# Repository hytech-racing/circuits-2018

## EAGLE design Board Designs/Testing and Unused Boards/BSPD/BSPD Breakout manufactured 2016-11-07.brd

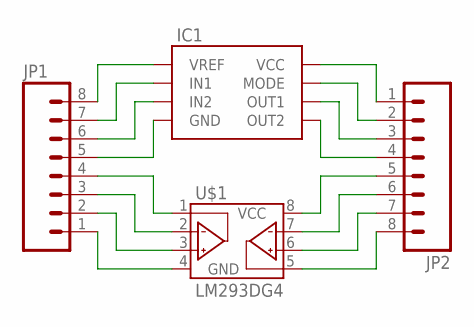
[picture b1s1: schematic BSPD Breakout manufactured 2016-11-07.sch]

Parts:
IC1: MC34161DG; SOIC-08
JP1, JP2: M08; 1X08
U$1: LM293DG4; SOIC-08

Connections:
unnamed: IC1.1 (VREF), JP1.8
unnamed: IC1.2 (IN1), JP1.7
unnamed: IC1.3 (IN2), JP1.6
unnamed: IC1.4 (GND), JP1.5
unnamed: IC1.5 (OUT2), JP2.4
unnamed: IC1.6 (OUT1), JP2.3
unnamed: IC1.7 (MODE), JP2.2
unnamed: IC1.8 (VCC), JP2.1
unnamed: JP2.5, U$1.8 (VCC)
unnamed: JP2.6, U$1.7 (2OUT)
unnamed: JP2.7, U$1.6 (2IN-)
unnamed: JP2.8, U$1.5 (2IN+)
unnamed: JP1.1, U$1.4 (GND)
unnamed: JP1.2, U$1.3 (1IN+)
unnamed: JP1.3, U$1.2 (1IN-)
unnamed: JP1.4, U$1.1 (1OUT)

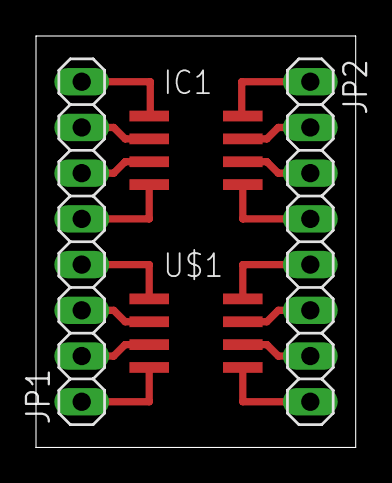
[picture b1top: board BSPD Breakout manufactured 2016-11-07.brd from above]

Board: 2 copper layers, 17.8 x 22.9 mm, 4 parts (0 on the bottom side), 16 nets.

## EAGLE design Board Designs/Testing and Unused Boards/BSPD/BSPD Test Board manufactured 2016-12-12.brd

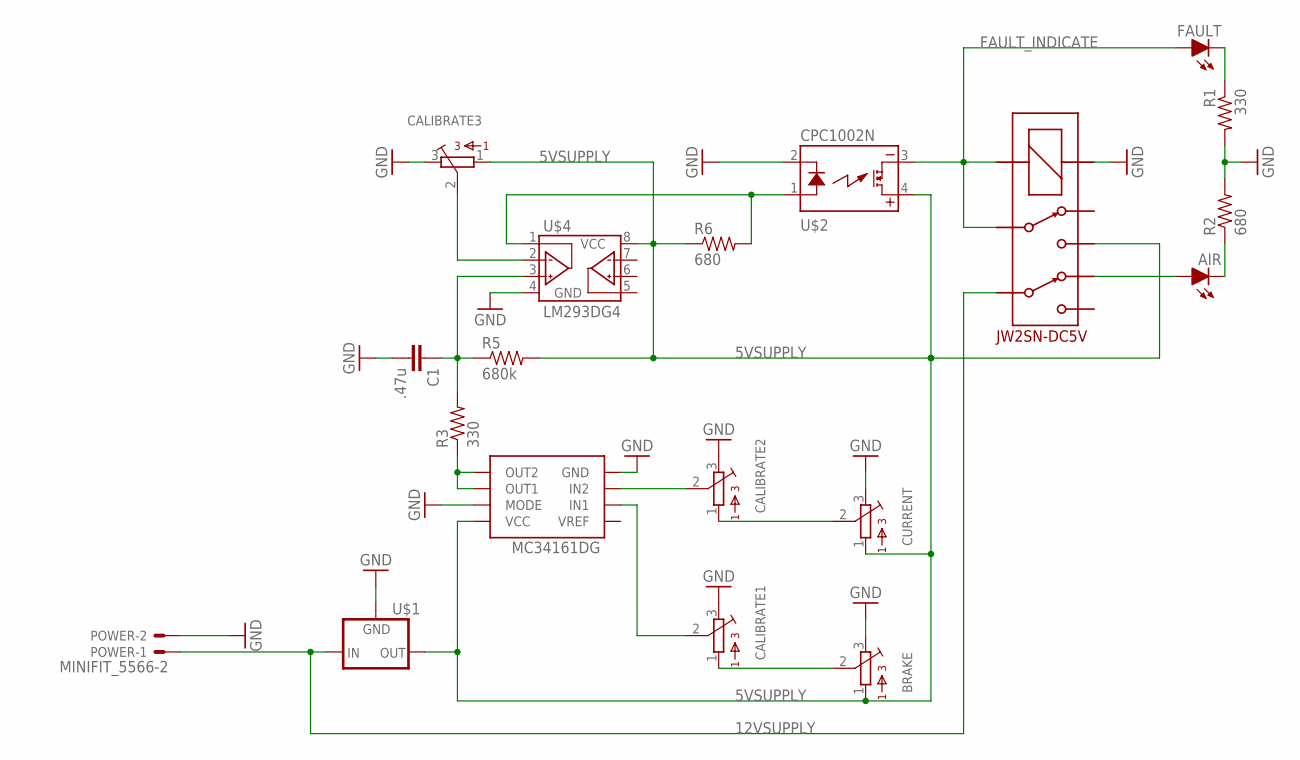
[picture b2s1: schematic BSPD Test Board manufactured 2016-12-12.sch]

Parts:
AIR: LED-5MM
BRAKE: TRIMPOT_3296C; TRIMPOT_3296
C1: .47u; CAP-PTH-SMALLEZ
CALIBRATE1, CALIBRATE2, CALIBRATE3: TRIMPOT_3296C; TRIMPOT_3296
CURRENT: TRIMPOT_3296C; TRIMPOT_3296
FAULT: LED-5MM
MC34161DG: MC34161DG; SOIC-08
POWER: MINIFIT_5566-2
R1, R3: 330; 0805
R2, R6: 680; 0805
R5: 680k; AXIAL-0.3EZ
U$1: 5V_REGULATOR_LM340-NLM340MPX-5.0/NOPB; SOT223
U$2: CPC1002N; SOP04
U$3: DPDT_RELAY_PANASONIC_JW2SN-DC5V; DPDT_RELAY_PANASONIC_JW2SN
U$4: LM293DG4; SOIC-08

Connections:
5VSUPPLY: BRAKE.1, CALIBRATE3.1, CURRENT.1, MC34161DG.8 (VCC), R5.P$2 (2), R6.1, U$1.3 (OUT), U$2.4 (DC+), U$3.4, U$4.8 (VCC)
12VSUPPLY: POWER.1, U$1.1 (IN), U$3.6
FAULT_INDICATE: FAULT.A, U$2.3 (DC-), U$3.3, U$3.COIL-
GND: BRAKE.3, C1.2, CALIBRATE1.3, CALIBRATE2.3, CALIBRATE3.3, CURRENT.3, MC34161DG.4 (GND), MC34161DG.7 (MODE), POWER.2, R1.2, R2.2, U$1.2 (GND), U$1.4 (GND), U$2.2 (CONTROL-), U$3.COIL+, U$4.4 (GND)
unnamed: FAULT.K (C), R1.1
unnamed: BRAKE.2, CALIBRATE1.1
unnamed: CALIBRATE2.1, CURRENT.2
unnamed: CALIBRATE2.2, MC34161DG.3 (IN2)
unnamed: CALIBRATE1.2, MC34161DG.2 (IN1)
unnamed: CALIBRATE3.2, U$4.2 (1IN-)
unnamed: R6.2, U$2.1 (CONTROL+), U$4.1 (1OUT)
unnamed: AIR.A, U$3.7
unnamed: AIR.K (C), R2.1
unnamed: C1.1, R3.2, R5.P$1 (1), U$4.3 (1IN+)
unnamed: MC34161DG.5 (OUT2), MC34161DG.6 (OUT1), R3.1

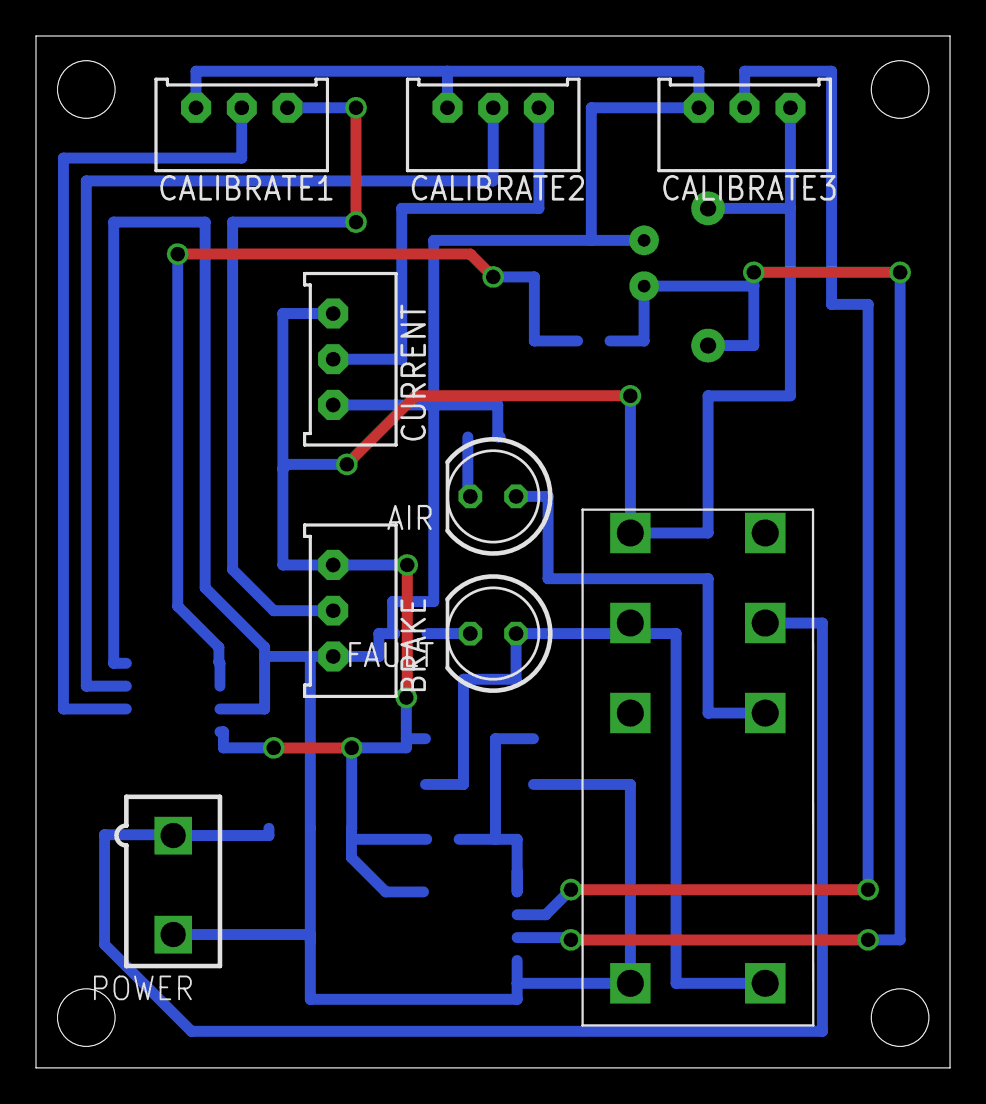
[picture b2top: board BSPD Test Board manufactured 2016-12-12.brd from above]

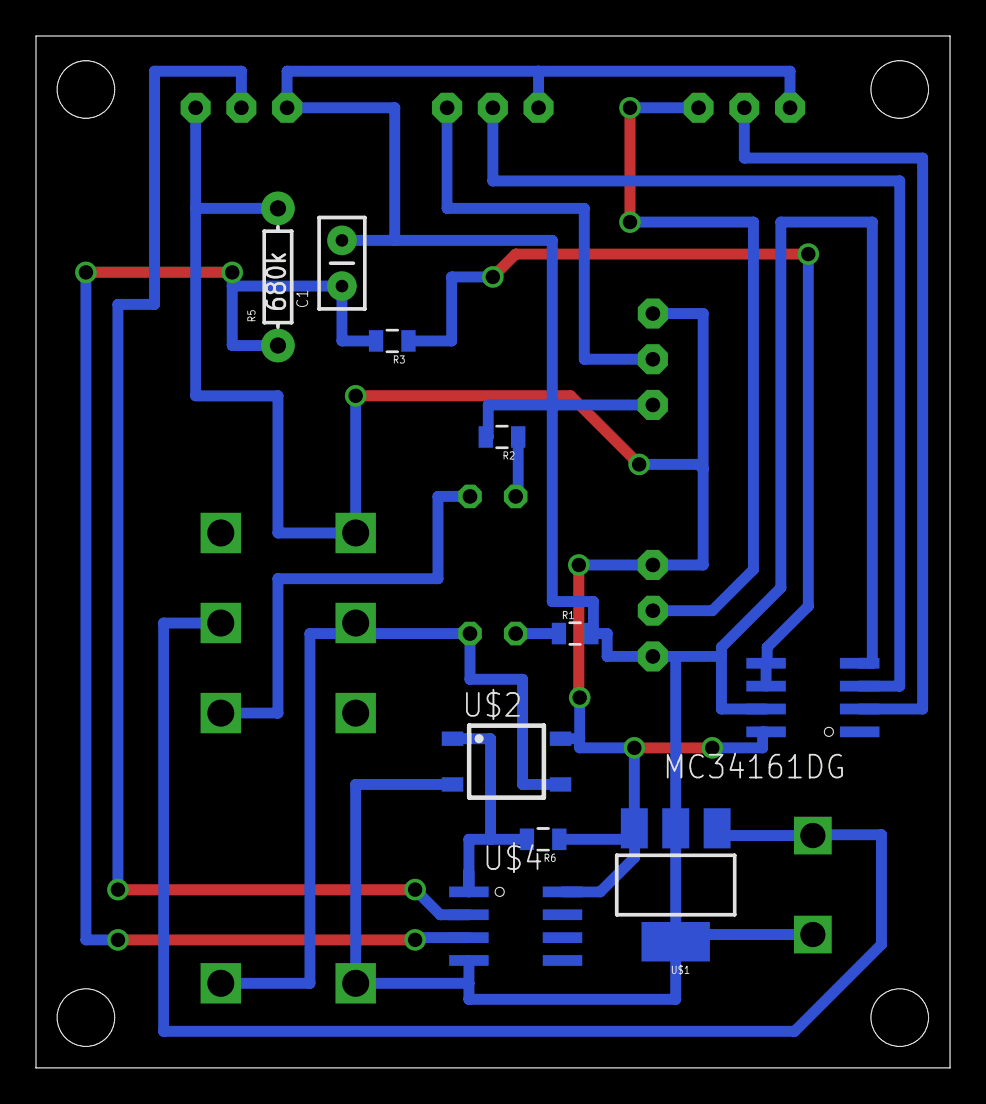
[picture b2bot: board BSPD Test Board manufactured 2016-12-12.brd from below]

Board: 2 copper layers, 50.8 x 57.3 mm, 19 parts (10 on the bottom side), 15 nets.

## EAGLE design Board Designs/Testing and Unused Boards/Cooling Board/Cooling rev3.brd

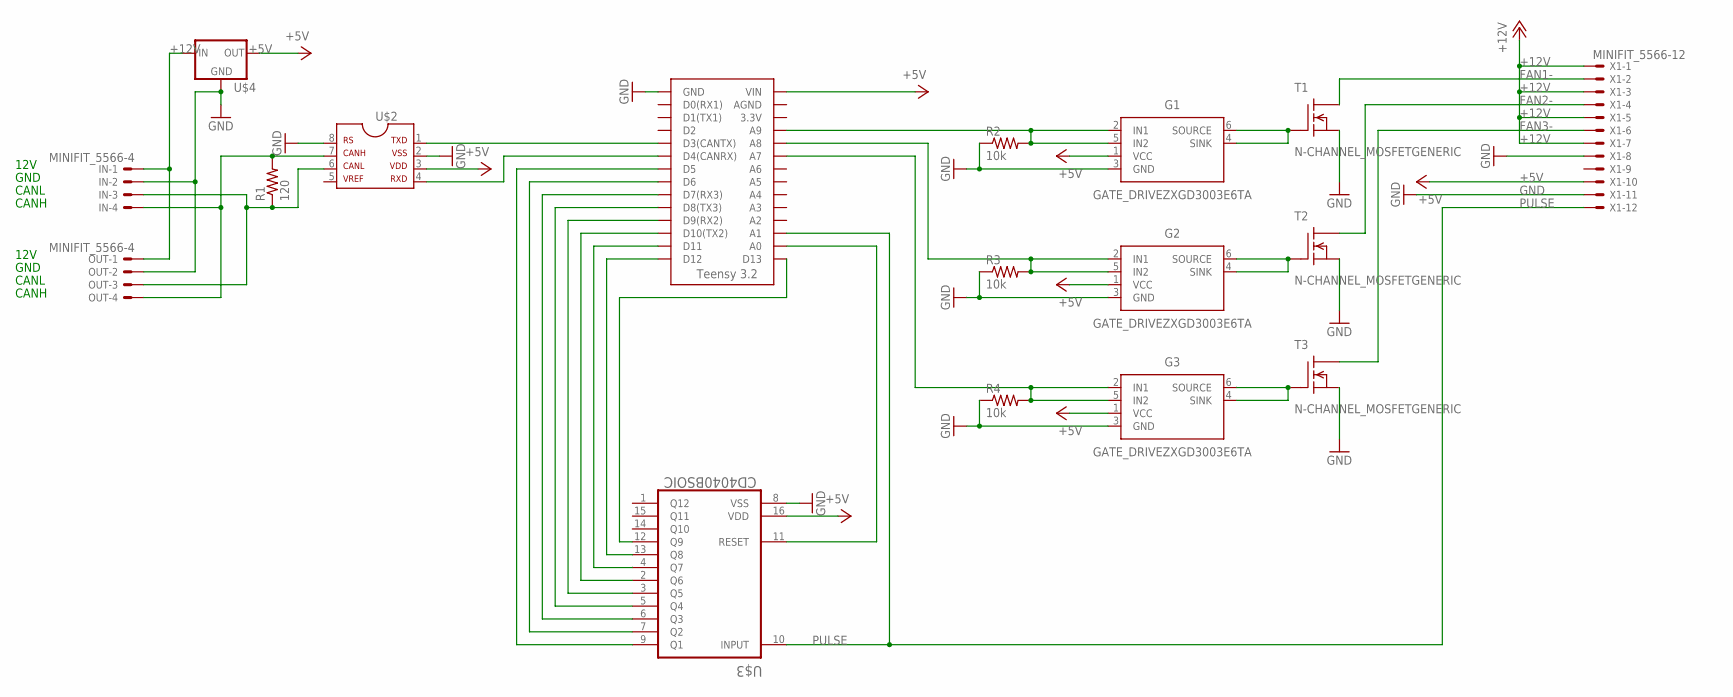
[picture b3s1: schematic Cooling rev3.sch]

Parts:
G1, G2, G3: GATE_DRIVEZXGD3003E6TA; SOT23-6
IN: MINIFIT_5566-4
OUT: MINIFIT_5566-4
R1: 120; 0805
R2, R3, R4: 10k; 0805
T1, T2, T3: N-CHANNEL_MOSFETGENERIC; TO-220-SINK
U$1: TEENSY_3.2_SIMPLE
U$2: MCP2551; SOIC-08
U$3: CD4040BSOIC; SOIC-16
U$4: 5V_REGULATOR_LM340-NLM340MPX-5.0/NOPB; SOT223
X1: MINIFIT_5566-12

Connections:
+5V: G1.1 (VCC), G2.1 (VCC), G3.1 (VCC), U$1.VIN, U$2.3, U$3.16 (VDD), U$4.3 (OUT), X1.10
+12V: IN.1, OUT.1, U$4.1 (IN), X1.1, X1.3, X1.5, X1.7
FAN1-: T1.2 (D), X1.2
FAN2-: T2.2 (D), X1.4
FAN3-: T3.2 (D), X1.6
GND: G1.3 (GND), G2.3 (GND), G3.3 (GND), IN.2, OUT.2, R2.1, R3.1, R4.1, T1.3 (S), T2.3 (S), T3.3 (S), U$1.GND, U$2.2, U$2.8, U$3.8 (VSS), U$4.2 (GND), U$4.4 (GND), X1.8, X1.11
unnamed: G1.4 (SINK), G1.6 (SOURCE), T1.1 (G)
unnamed: U$1.D3(CANTX), U$2.1
unnamed: U$1.D4(CANRX), U$2.4
unnamed: G2.4 (SINK), G2.6 (SOURCE), T2.1 (G)
unnamed: G3.4 (SINK), G3.6 (SOURCE), T3.1 (G)
unnamed: IN.3, OUT.3, R1.1, U$2.6
unnamed: IN.4, OUT.4, R1.2, U$2.7
unnamed: U$1.D5, U$3.9 (Q1)
unnamed: U$1.D6, U$3.7 (Q2)
unnamed: U$1.D7(RX3), U$3.6 (Q3)
unnamed: U$1.D8(TX3), U$3.5 (Q4)
unnamed: U$1.D9(RX2), U$3.3 (Q5)
unnamed: U$1.D10(TX2), U$3.2 (Q6)
unnamed: G1.2 (IN1), G1.5 (IN2), R2.2, U$1.A9
unnamed: G2.2 (IN1), G2.5 (IN2), R3.2, U$1.A8
unnamed: G3.2 (IN1), G3.5 (IN2), R4.2, U$1.A7
unnamed: U$1.D11, U$3.4 (Q7)
unnamed: U$1.D12, U$3.13 (Q8)
unnamed: U$1.A0, U$3.11 (RESET)
unnamed: U$1.D13, U$3.12 (Q9)
PULSE: U$1.A1, U$3.10 (INPUT), X1.12

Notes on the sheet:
12V
GND
CANL
CANH

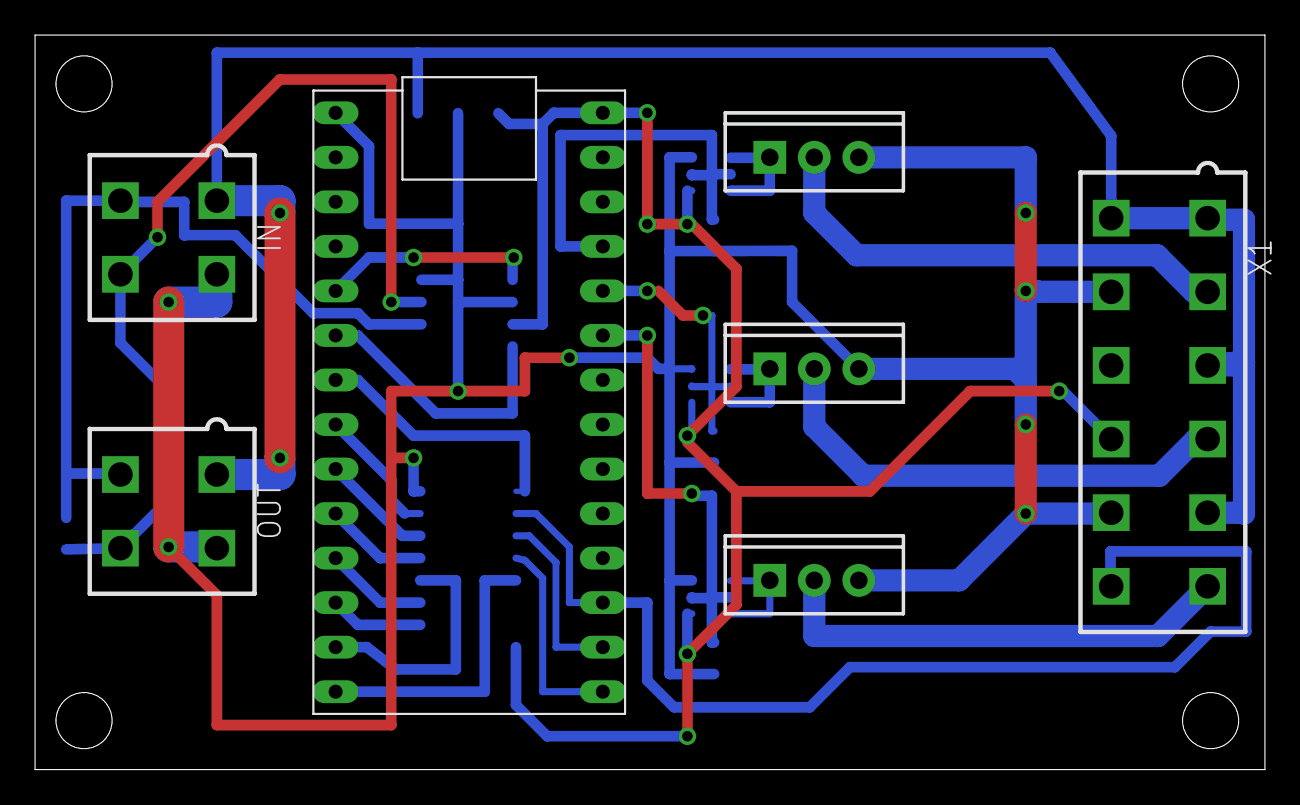
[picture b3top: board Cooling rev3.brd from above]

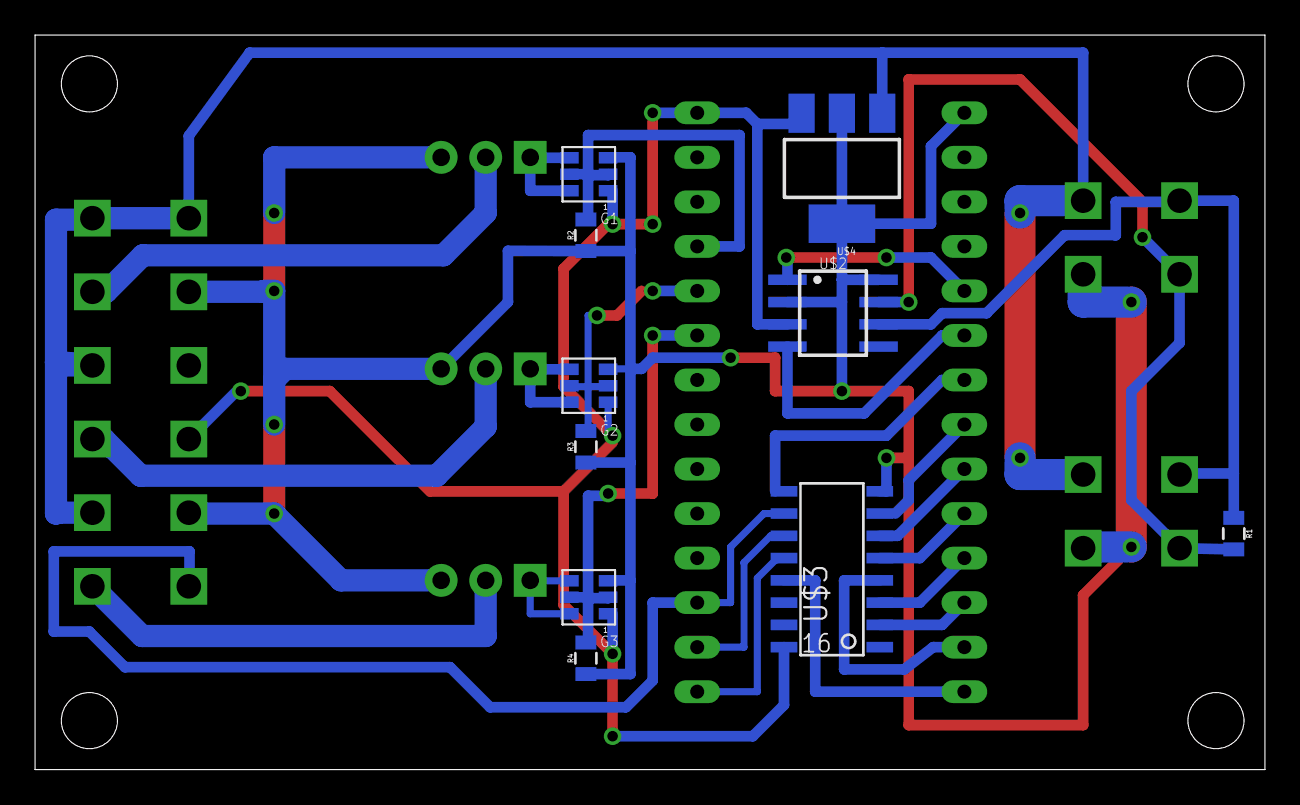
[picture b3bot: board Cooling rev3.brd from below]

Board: 2 copper layers, 70.2 x 41.9 mm, 17 parts (10 on the bottom side), 27 nets.

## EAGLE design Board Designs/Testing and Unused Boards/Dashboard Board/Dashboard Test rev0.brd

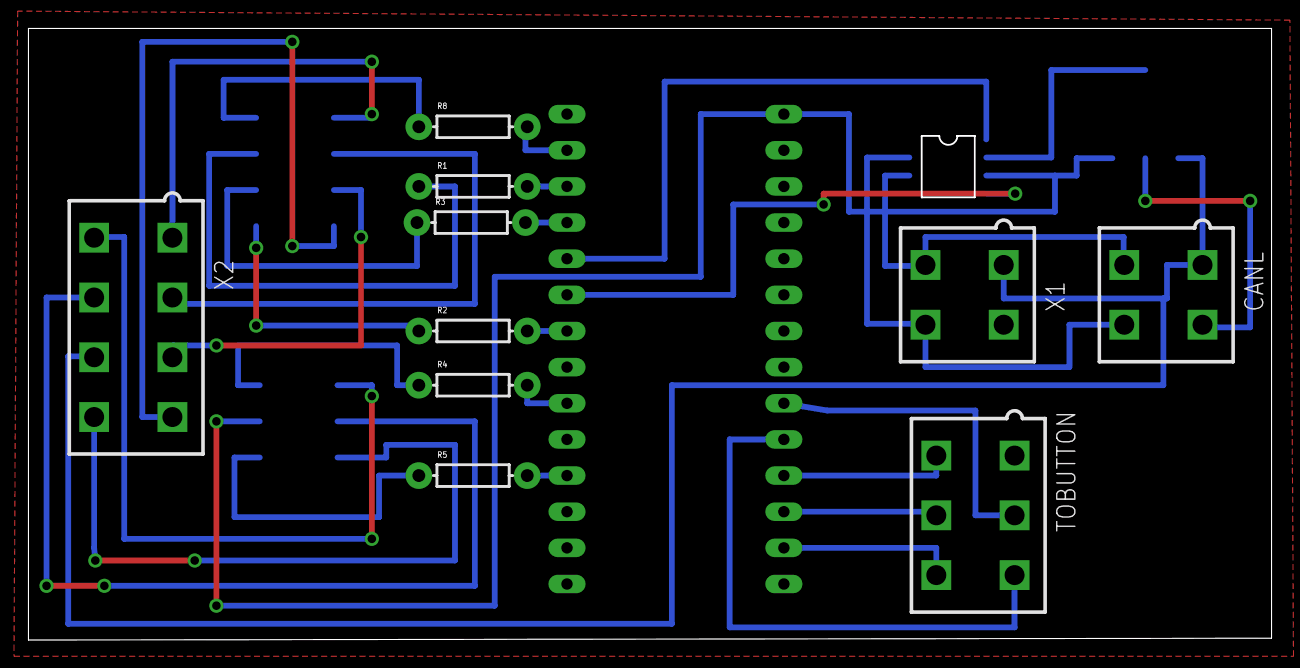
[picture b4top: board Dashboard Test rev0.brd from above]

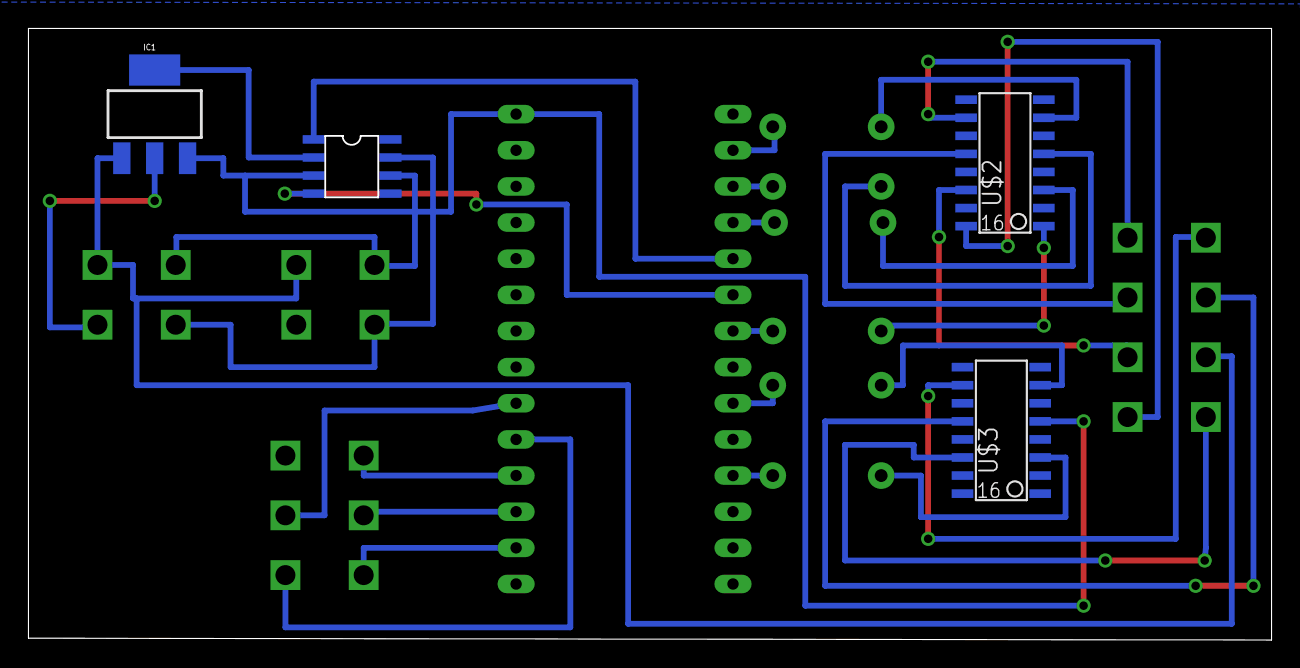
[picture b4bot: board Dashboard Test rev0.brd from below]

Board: 2 copper layers, 87.4 x 43.0 mm, 15 parts (4 on the bottom side), 31 nets.

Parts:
CAN: MCP2551SOIC; SOIC08
CANL: MINIFIT_5566-4
IC1: SOT223
R1, R2, R3, R4, R5, R8: AXIAL-0.3
TOBUTTON: MINIFIT_5566-6
U$1: TEENSY_3.2_SIMPLE
U$2: OPTOCOUPLER_QUAD_TLP291-4; SO-16
U$3: TLP291-4; SOIC-16
X1: MINIFIT_5566-4
X2: MINIFIT_5566-8

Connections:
12VSUPPLY: CANL.1, IC1.1, X1.1, X2.7
BOOST: TOBUTTON.3, U$1.A3
BUZZER: U$3.14, X2.8
CANH: CAN.6, CANL.3, X1.3
CANL: CAN.7, CANL.4, X1.4
GND: CAN.2, CAN.8, CANL.2, IC1.2, IC1.4, U$1.GND, U$2.2, U$2.4, U$2.6, U$2.8, U$2.9, U$2.11, U$2.13, U$2.15, U$3.2, U$3.4, U$3.6, U$3.8, U$3.9, U$3.11, U$3.13, U$3.15, X1.2
LED_BMS: U$3.12, X2.6
LED_BOOST: U$2.12, X2.2
LED_BSPD: U$2.16, X2.4
LED_IMD: U$3.10, X2.5
LED_MARK: U$2.10, X2.1
LED_START: U$2.14, X2.3
MARK: TOBUTTON.2, U$1.A4
unnamed: R3.P$2, U$1.D2
unnamed: CAN.1, U$1.D3(CANTX)
unnamed: CAN.4, U$1.D4(CANRX)
unnamed: R3.P$1, U$2.3
unnamed: R1.P$2, U$1.D1(TX1)
unnamed: R4.P$1, U$3.7
unnamed: R2.P$1, U$2.1
unnamed: R1.P$1, U$2.5
unnamed: R8.P$2, U$1.D0(RX1)
unnamed: R8.P$1, U$2.7
unnamed: R2.P$2, U$1.D5
unnamed: R4.P$2, U$1.D7(RX3)
unnamed: R5.P$2, U$1.D9(RX2)
unnamed: CAN.3, IC1.3, U$1.VIN, U$3.5
unnamed: R5.P$1, U$3.3
SELECT: TOBUTTON.6, U$1.A0
START: TOBUTTON.4, U$1.A2
TOGGLE: TOBUTTON.5, U$1.A1

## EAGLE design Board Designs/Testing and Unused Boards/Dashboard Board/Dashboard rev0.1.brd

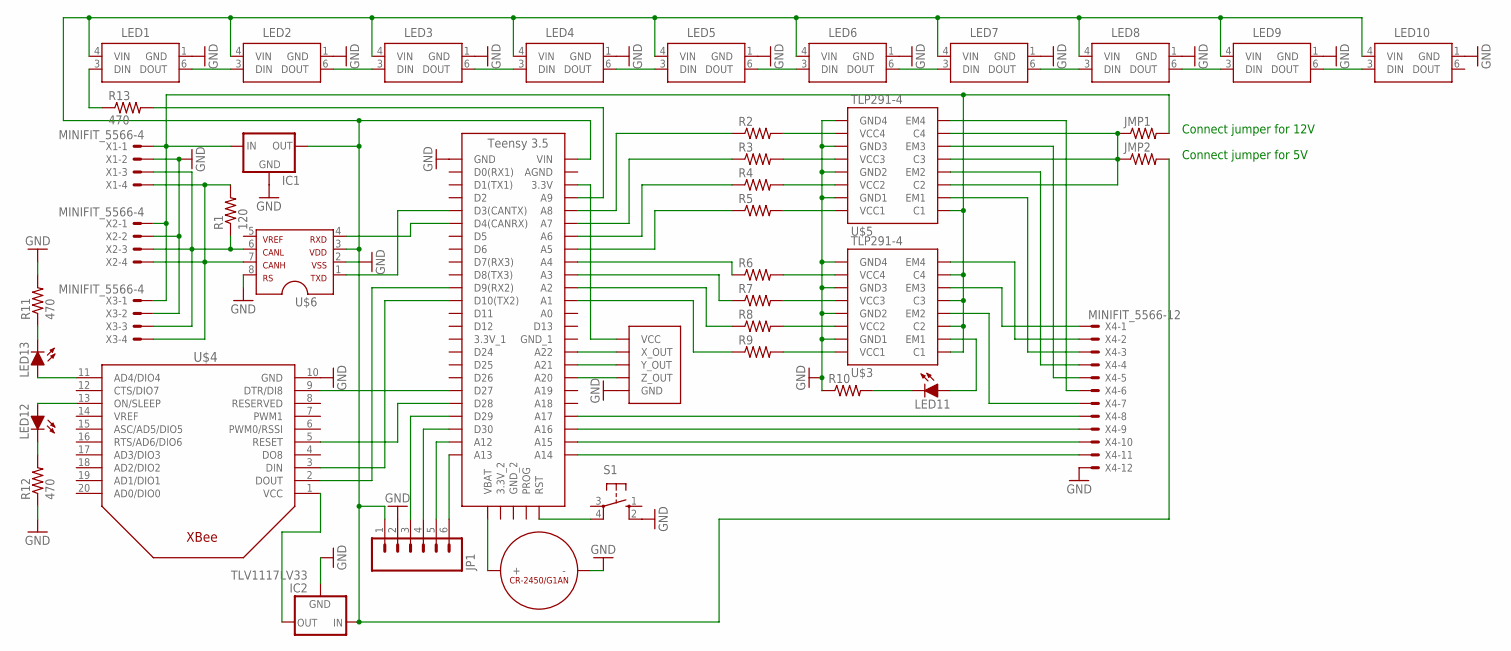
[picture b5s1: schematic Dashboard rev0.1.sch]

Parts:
IC1: 5VREG_L7805_HOR; TO-220-H
IC2: TLV1117LV33; SOT223
JMP1, JMP2: RESISTORPTH-1/4W-VERT; AXIAL-0.1
JP1: M06; 1X06
LED1, LED2, LED3, LED4, LED5, LED6, LED7, LED8, LED9, LED10: WS2812B5050; RGBLED5050
LED11, LED12, LED13: LED-0805; LED-805
R1: 120; 0805
R2, R3, R4, R5, R6, R7, R8, R9, R10: RESISTOR0805-RES; 0805
R11, R12, R13: 470; 0805
S1: BTN_10-XX; B3F-10XX
U$1: TEENSY_3.5_SIMPLE_RTC
U$2: CR-2450/G1AN
U$3, U$5: TLP291-4; SOIC-16
U$4: XBEE
U$6: MCP2551; SOIC-08
U$7: ADXL335
X1, X2, X3: MINIFIT_5566-4
X4: MINIFIT_5566-12

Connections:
GND: IC1.2 (GND), IC2.1 (GND), JP1.2, LED1.1 (GND), LED2.1 (GND), LED3.1 (GND), LED4.1 (GND), LED5.1 (GND), LED6.1 (GND), LED7.1 (GND), LED8.1 (GND), LED9.1 (GND), LED10.1 (GND), R10.1, R11.2, R12.1, S1.2 (S1), U$1.GND, U$2.-, U$3.2 (GND1), U$3.4 (GND2), U$3.6 (GND3), U$3.8 (GND4), U$4.10 (GND), U$5.2 (GND1), U$5.4 (GND2), U$5.6 (GND3), U$5.8 (GND4), U$6.2, U$6.8, U$7.GND, X1.2, X2.2, X3.2, X4.12
unnamed: U$1.VBAT, U$2.+_0 (+), U$2.+_1 (+)
unnamed: R2.2, U$5.7 (VCC4)
unnamed: LED1.6 (DOUT), LED2.3 (DIN)
unnamed: LED2.6 (DOUT), LED3.3 (DIN)
unnamed: LED3.6 (DOUT), LED4.3 (DIN)
unnamed: LED4.6 (DOUT), LED5.3 (DIN)
unnamed: LED5.6 (DOUT), LED6.3 (DIN)
unnamed: LED6.6 (DOUT), LED7.3 (DIN)
unnamed: LED7.6 (DOUT), LED8.3 (DIN)
unnamed: LED8.6 (DOUT), LED9.3 (DIN)
unnamed: LED9.6 (DOUT), LED10.3 (DIN)
unnamed: R3.2, U$5.5 (VCC3)
unnamed: U$1.D3(CANTX), U$6.1
unnamed: IC1.1 (IN), JMP1.P$2 (2), U$3.10 (C4), U$3.12 (C3), U$3.14 (C2), U$3.16 (C1), U$5.16 (C1), X1.1, X2.1, X3.1
unnamed: U$1.D4(CANRX), U$6.4
unnamed: R1.1, U$6.6, X1.3, X2.3, X3.3
unnamed: R1.2, U$6.7, X1.4, X2.4, X3.4
unnamed: LED12.A, U$4.13 (ON/SLEEP)
unnamed: R13.2, U$1.A9
unnamed: R2.1, U$1.A8
unnamed: R3.1, U$1.A7
unnamed: R4.1, U$1.A6
unnamed: R5.1, U$1.A5
unnamed: R6.1, U$1.A4
unnamed: R7.1, U$1.A3
unnamed: R8.1, U$1.A2
unnamed: R9.1, U$1.A1
unnamed: R4.2, U$5.3 (VCC2)
unnamed: R5.2, U$5.1 (VCC1)
unnamed: R6.2, U$3.7 (VCC4)
unnamed: R7.2, U$3.5 (VCC3)
unnamed: R8.2, U$3.3 (VCC2)
unnamed: R9.2, U$3.1 (VCC1)
unnamed: JMP1.P$1 (1), JMP2.P$1 (1), U$5.10 (C4), U$5.12 (C3), U$5.14 (C2)
unnamed: U$1.3.3V, U$7.VCC
unnamed: U$1.A22, U$7.X_OUT
unnamed: U$1.A21, U$7.Y_OUT
unnamed: U$1.A20, U$7.Z_OUT
unnamed: S1.4 (P1), U$1.RST
unnamed: U$1.D28, U$4.5 (RESET)
unnamed: U$1.A14, X4.11
unnamed: U$1.A16, X4.9
unnamed: U$5.9 (EM4), X4.6
unnamed: U$5.11 (EM3), X4.5
unnamed: U$5.13 (EM2), X4.4
unnamed: U$5.15 (EM1), X4.3
unnamed: U$3.9 (EM4), X4.2
unnamed: U$3.11 (EM3), X4.1
unnamed: U$3.13 (EM2), X4.7
unnamed: LED11.A, U$3.15 (EM1)
unnamed: U$1.A17, X4.8
unnamed: U$1.A15, X4.10
unnamed: U$1.D9(RX2), U$4.2 (DOUT)
unnamed: U$1.D10(TX2), U$4.3 (DIN)
unnamed: U$1.D27, U$4.9 (DTR/DI8)
unnamed: LED11.C, R10.2
unnamed: LED13.A, U$4.11 (AD4/DIO4)
unnamed: LED13.C, R11.1
unnamed: LED12.C, R12.2
unnamed: IC1.3 (OUT), IC2.3 (IN), JMP2.P$2 (2), JP1.1, LED1.4 (VIN), LED2.4 (VIN), LED3.4 (VIN), LED4.4 (VIN), LED5.4 (VIN), LED6.4 (VIN), LED7.4 (VIN), LED8.4 (VIN), LED9.4 (VIN), LED10.4 (VIN), U$1.VIN, U$6.3
unnamed: JP1.5, U$1.A12
unnamed: JP1.4, U$1.D30
unnamed: JP1.3, U$1.D29
unnamed: JP1.6, U$1.A13
unnamed: LED1.3 (DIN), R13.1
VCC: IC2.2 (OUT), IC2.4 (OUT), U$4.1 (VCC)

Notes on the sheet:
Connect jumper for 5V
Connect jumper for 12V

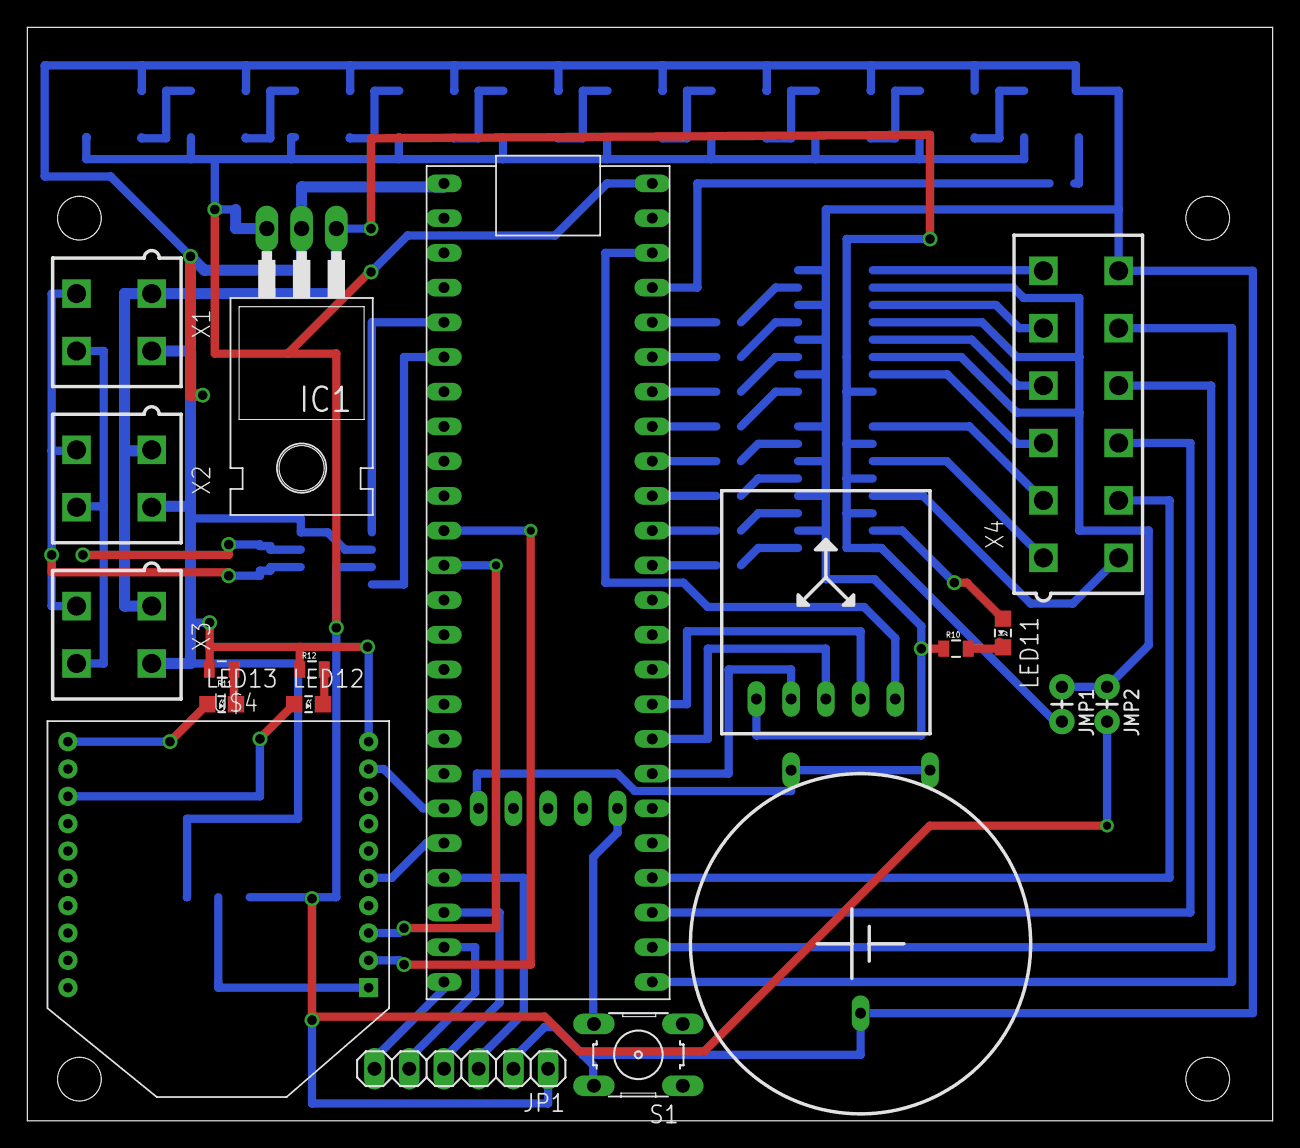
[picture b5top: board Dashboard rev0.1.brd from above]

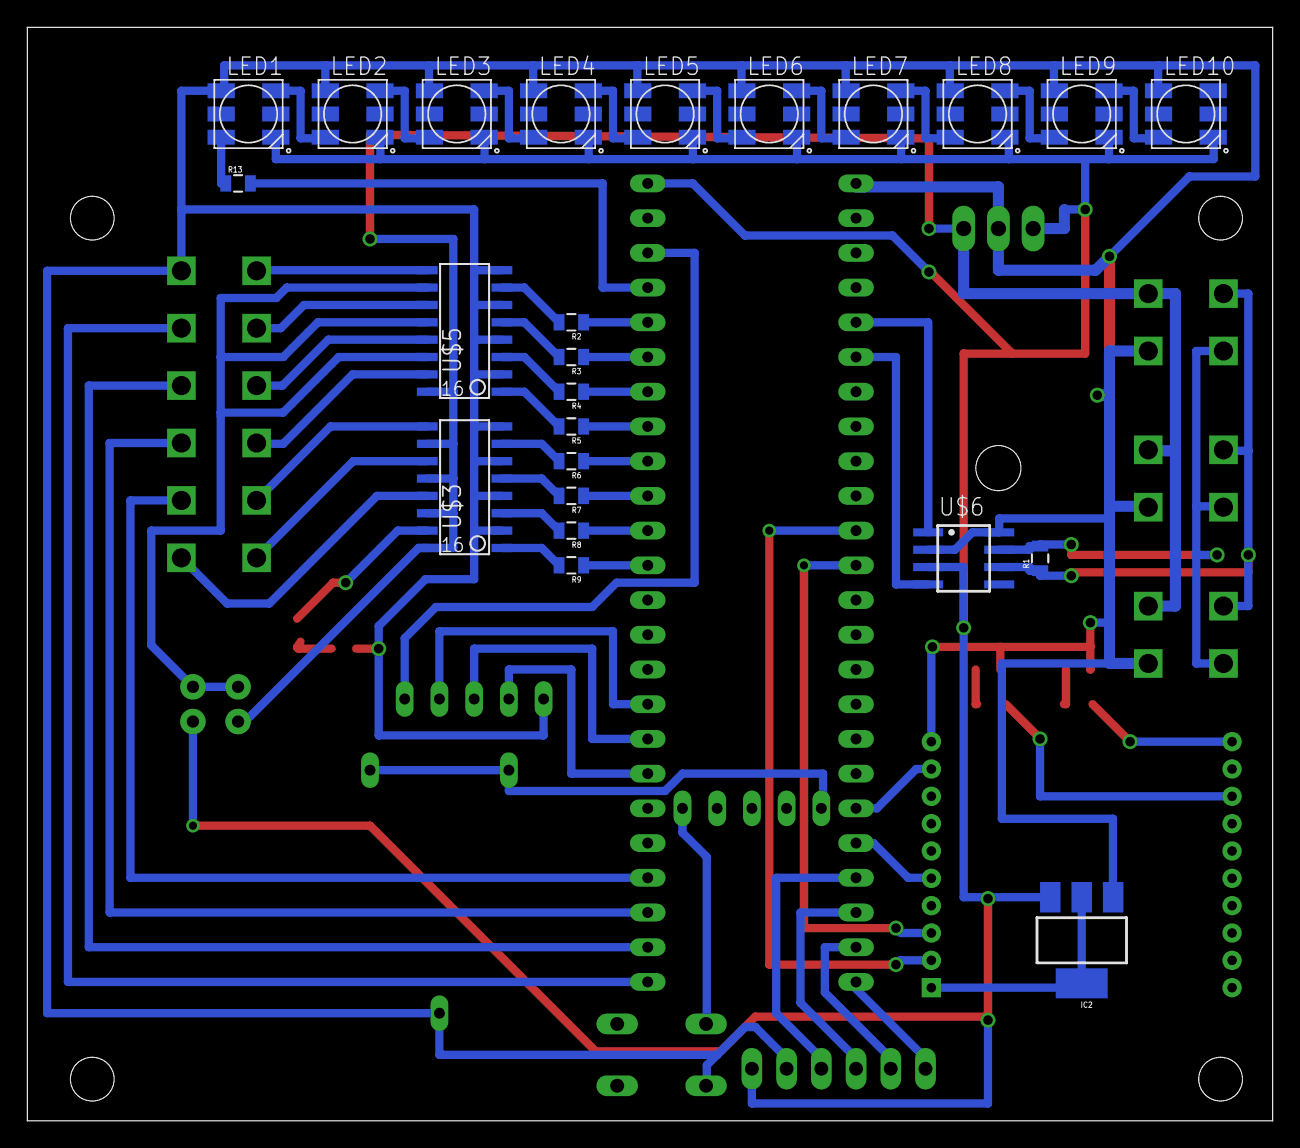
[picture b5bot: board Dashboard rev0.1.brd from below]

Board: 2 copper layers, 91.1 x 80.0 mm, 43 parts (24 on the bottom side), 67 nets.

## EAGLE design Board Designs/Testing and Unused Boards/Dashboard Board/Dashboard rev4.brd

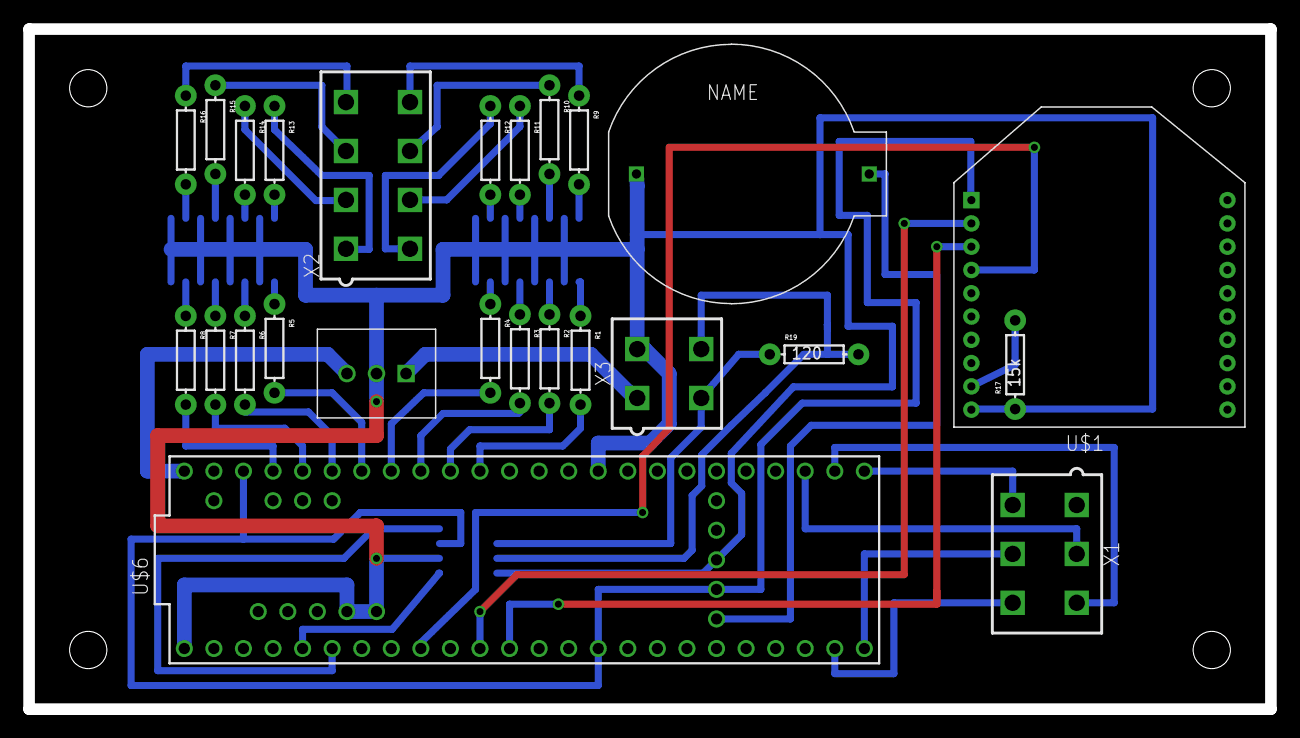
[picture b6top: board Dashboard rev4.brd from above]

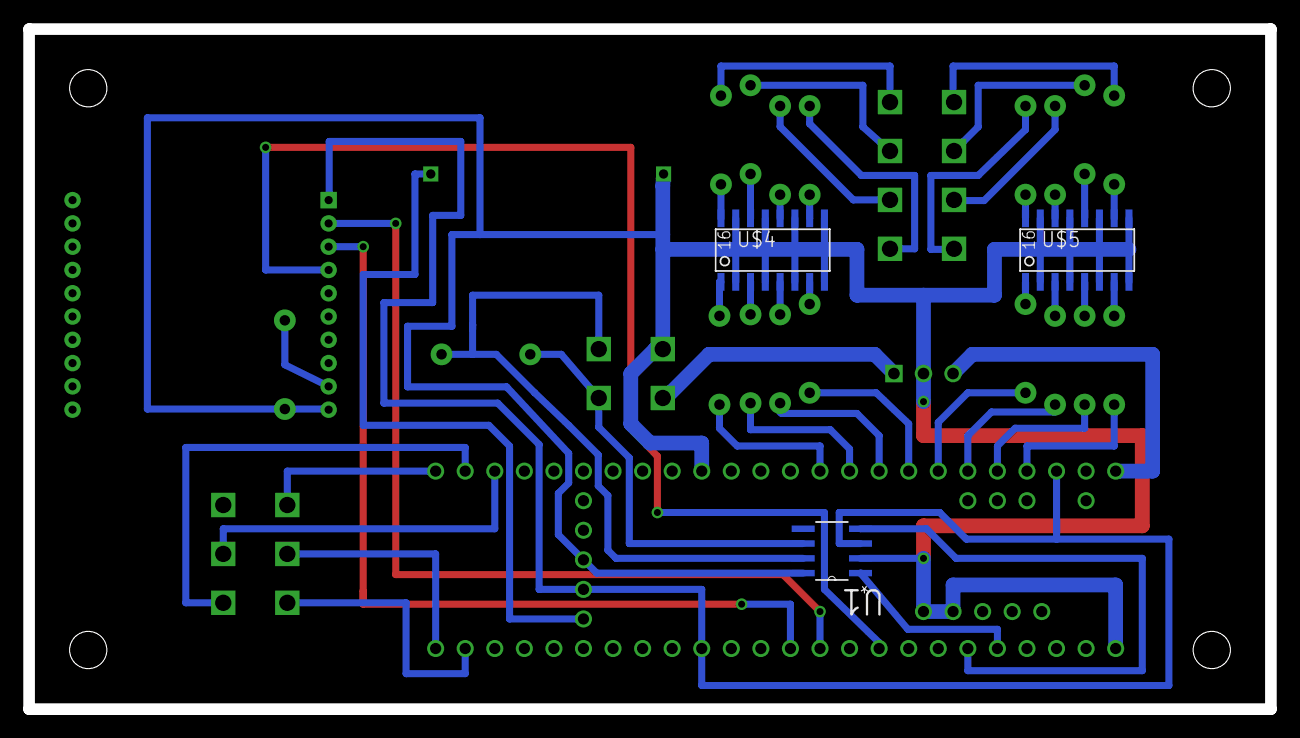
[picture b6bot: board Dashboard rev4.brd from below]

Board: 2 copper layers, 106.7 x 58.4 mm, 28 parts (3 on the bottom side), 50 nets.

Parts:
IC1: TO-220-SPACED
R1, R2, R3, R4, R5, R6, R7, R8, R9, R10, R11, R12, R13, R14, R15, R16: AXIAL-0.3
R17: 15k; AXIAL-0.3
R19: 120; AXIAL-0.3
U1: SN65HVD230D; SOIC127P600X175-8N
U$1: XBEE
U$2: COIN-CELL-HOLDER
U$4, U$5: TLP291-4; SOIC-16
U$6: TEENSY_3.5_ALL_PINS
X1: CONNECTOR-6; MINIFIT_5566-6
X2: CONNECTOR-8; MINIFIT_5566-8
X3: CONNECTOR-4; MINIFIT_5566-4

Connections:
GND: IC1.2, R17.P$1, U1.2, U1.8, U$1.10, U$2.GND, U$4.2, U$4.4, U$4.6, U$4.8, U$4.9, U$4.11, U$4.13, U$4.15, U$5.2, U$5.4, U$5.6, U$5.8, U$5.9, U$5.11, U$5.13, U$5.15, U$6.GND, U$6.GND1, U$6.GND3, U$6.GND4, U$6.GND6, X3.2
unnamed: R9.P$1, X2.8
unnamed: U$1.2, U$6.9
unnamed: R10.P$1, X2.7
unnamed: R11.P$1, X2.6
unnamed: R1.P$1, U$4.1
unnamed: R12.P$1, X2.5
unnamed: R2.P$1, U$4.3
unnamed: R3.P$1, U$4.5
unnamed: U$1.3, U$6.10
unnamed: U$1.4, U$6.7
unnamed: R4.P$1, U$4.7
unnamed: R5.P$1, U$5.1
unnamed: R17.P$2, U$1.9
unnamed: R6.P$1, U$5.3
unnamed: R7.P$1, U$5.5
unnamed: R8.P$1, U$5.7
unnamed: U$6.31/A12, X1.6
unnamed: R13.P$1, X2.1
unnamed: U$6.32/A13, X1.5
unnamed: U$6.33/A14, X1.4
unnamed: U$6.34/A15, X1.3
unnamed: U$6.35/A16, X1.2
unnamed: U$2.VDD, U$6.VBAT
unnamed: U1.1, U$6.3
unnamed: R9.P$2, U$4.16
unnamed: R10.P$2, U$4.14
unnamed: R11.P$2, U$4.12
unnamed: R12.P$2, U$4.10
unnamed: R13.P$2, U$5.16
unnamed: R14.P$2, U$5.14
unnamed: R15.P$2, U$5.12
unnamed: R16.P$2, U$5.10
unnamed: R14.P$1, X2.2
unnamed: R15.P$1, X2.3
unnamed: R16.P$1, X2.4
unnamed: U1.4, U$6.4
unnamed: R19.P$2, U1.7, X3.4
unnamed: R1.P$2, U$6.16/A2
unnamed: R2.P$2, U$6.17/A3
unnamed: R3.P$2, U$6.18/A4
unnamed: R19.P$1, U1.6, X3.3
unnamed: IC1.3, U$6.VIN
unnamed: IC1.1, X3.1
unnamed: R4.P$2, U$6.19/A5
unnamed: R5.P$2, U$6.20/A6
unnamed: R6.P$2, U$6.21/A7
unnamed: R7.P$2, U$6.22/A8
unnamed: R8.P$2, U$6.23/A9
VCC: U1.3, U$1.1, U$6.3.3V, U$6.3.3V3, U$6.3.3V4
